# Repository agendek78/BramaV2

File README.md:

# BramaV2

**English** | [Polski](README.pl.md)

Gate control over Bluetooth LE: an Android app (with Android Auto support) and ESP32 controller firmware.
The phone is the BLE central; the ESP32 is the peripheral that drives two separate outputs (OPEN and CLOSE)
of the gate operator.

> **Status: prototype.** The project is tested on a single prototype board and three phones. It controls a
> physical device (a moving gate), so verify it yourself before using it in a real installation. Firmware images
> are signed with a development key; production Secure Boot, flash encryption and production keys are not part
> of this repository.

## What it does

- Two commands: `OPEN` (with optional automatic close after the connection is lost) and `CLOSE`.
- The gate position is always unknown: an acknowledgement only means that a pulse was driven on the output.
- Pairing with a QR code or the controller's 6-digit PIN (EC-JPAKE); the session is encrypted and authenticated
  with AES-256-GCM.
- Up to 8 authorized phones at the same time; the app can list phones, remove them and rename the current one.
- Automatic close is performed by the controller, without any involvement of the phone.
- Firmware update over BLE (OTA): signed ECDSA P-256 image, protection against an older `secure_version`,
  rollback to the previous version after a failed boot.
- Android Auto displays the interface of the app running on the phone.

## Repository layout

| Directory | Contents |
|---|---|
| `app/` | Android app (Kotlin, Jetpack Compose): screens and services |
| `protocol/` | Wire protocol: frames, cryptography, EC-JPAKE, test vectors |
| `domain/` | App logic, gate state and repository (no Android dependencies) |
| `ble/` | BLE layer (Android) and a simulated controller for tests |
| `car/` | Android Auto (Car App Library) |
| `firmware/` | ESP32 firmware (ESP-IDF v6.0.1, NimBLE) and host-side tests |
| `hw/` | PCB project in KiCad 10 (schematic, board, interactive BOM) |
| `doc/` | Specification, module designs, plans and implementation status |

The documentation is written in Polish. Good places to start:

- [`doc/PLAN_I_SPECYFIKACJA_BRAMY.md`](doc/PLAN_I_SPECYFIKACJA_BRAMY.md): specification and protocol,
- [`doc/implementation_status.md`](doc/implementation_status.md): what is done and verified (including on hardware),
- [`firmware/README.md`](firmware/README.md): firmware build, tests and configuration.

## Android app

Requirements: Android Studio with a JDK, Android SDK 37 (`compileSdk`), and a device running Android 13 (API 33)
or newer with Bluetooth LE. The QR scanner relies on Google Play services.

```sh
./gradlew :app:assembleDebug        # debug build
./gradlew :app:assembleRelease      # release build (R8, unsigned: the APK has to be signed)
./gradlew test                      # unit tests of all modules
```

The release build has R8 and resource shrinking enabled (about 4 MB). Keep rules for ML Kit are in
`app/proguard-rules.pro`. The repository contains no release signing configuration.

## Firmware

Requirements: ESP-IDF v6.0.1 (`~/.espressif/v6.0.1/esp-idf`) and a development key for signing the image.

```sh
cd firmware
tools/gen_dev_signing_key.sh        # once: key in ~/.config/brama/ (outside the repository)
tools/idf.sh set-target esp32       # once
tools/idf.sh build                  # produces the signed build/brama.bin
```

Host-side logic tests (target `linux`, need the `libbsd-dev` package):

```sh
cd firmware/test/host
../../tools/idf.sh --preview set-target linux
../../tools/idf.sh build && ./build/brama_host_test.elf
```

Details (prototype pins, service mode, UART console, OTA) are in [`firmware/README.md`](firmware/README.md).

**A note on eFuse.** On the board in `hw/`, GPIO12 has a pull-up that selects 1.8 V flash voltage at reset, while
the ESP32-WROOM-32D module has 3.3 V flash. The 3.3 V flash-voltage eFuse is therefore burned on every such board
(an irreversible step, done manually before the first boot; see `firmware/README.md`).

## Hardware

The board design is in `hw/` (KiCad 10, open `hw/esp32_brama.kicad_pro`): ESP32-WROOM-32D, power from an LMR54410
buck converter, two OPEN/CLOSE outputs through CNY17 optocouplers, an interlock input and a UART for diagnostics.
The project libraries are in `hw/lib/`. Notes from the board review are in `doc/implementation_status.md`.

## License

[MIT](LICENSE). The project is developed and tested by a single person; contributions and feedback are welcome.

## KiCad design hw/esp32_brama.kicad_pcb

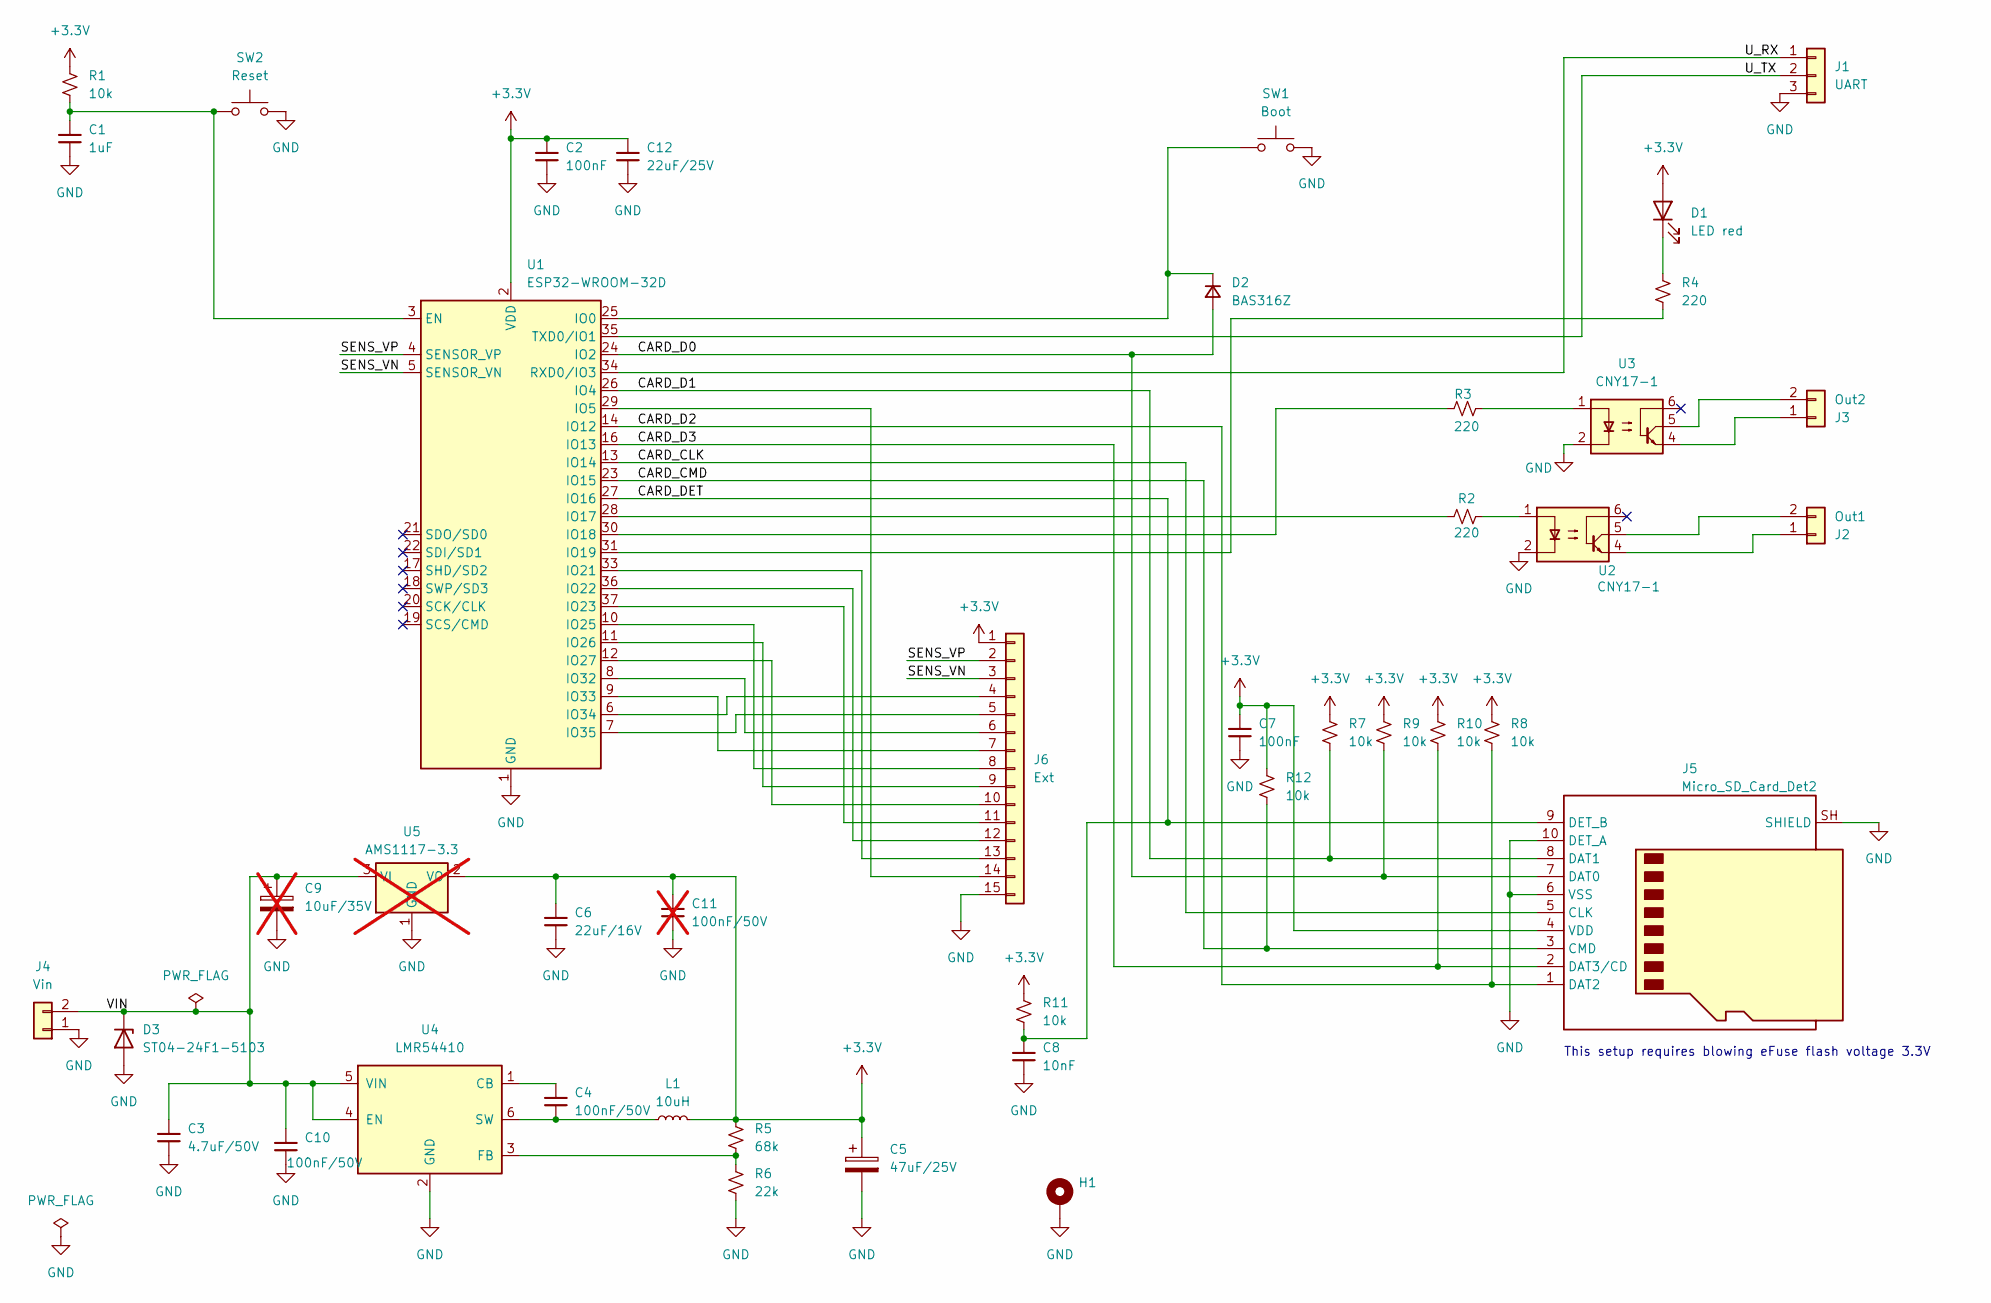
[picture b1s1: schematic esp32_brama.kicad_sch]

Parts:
C1: 1uF; C_0402_1005Metric
C2, C7: 100nF; C_0402_1005Metric
C3: 4.7uF/50V; C_0603_1608Metric
C4, C10: 100nF/50V; C_0402_1005Metric
C5: 47uF/25V; CP_Radial_D6.3mm_P2.50mm
C6: 22uF/16V; C_0805_2012Metric
C8: 10nF; C_0402_1005Metric
C9: 10uF/35V; CP_Radial_D6.3mm_P2.50mm; not fitted
C11: 100nF/50V; C_0402_1005Metric; not fitted
C12: 22uF/25V; C_0805_2012Metric
D1: LED red; D_0603_1608Metric
D2: BAS316Z; D_SOD-323_HandSoldering
D3: ST04-24F1-5103; D_SMA
H1: MountingHole_Pad; MountingHole_3.2mm_M3_ISO14580_Pad
J1: UART; PinHeader_1x03_P2.54mm_Vertical
J2: Out1; TerminalBlock_4Ucon_1x02_P3.50mm_Horizontal
J3: Out2; TerminalBlock_4Ucon_1x02_P3.50mm_Horizontal
J4: Vin; TerminalBlock_4Ucon_1x02_P3.50mm_Horizontal
J5: Micro_SD_Card_Det2; SD_MICRO
J6: Ext; PinHeader_1x15_P2.54mm_Vertical
L1: 10uH; L_Bourns-SRN4018
R1, R7, R8, R9, R10, R11, R12: 10k; R_0402_1005Metric
R2, R3, R4: 220; R_0402_1005Metric
R5: 68k; R_0402_1005Metric
R6: 22k; R_0402_1005Metric
SW1: Boot; SW_Tactile_SPST_NO_Straight_CK_PTS636Sx25SMTRLFS
SW2: Reset; SW_Tactile_SPST_NO_Straight_CK_PTS636Sx25SMTRLFS
U1: ESP32-WROOM-32D; ESP32-WROOM-32U
U2, U3: CNY17-1; DIP-6_W7.62mm
U4: LMR54410; SOT-23-6
U5: AMS1117-3.3; SOT-223-3_TabPin2; not fitted

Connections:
+3.3V: C2.1, C5.1, C6.1, C7.1, C11.1, C12.1, D1.2 (A), J5.4 (VDD), J6.1, L1.2, R1.1, R5.1, R7.1, R8.1, R9.1, R10.1, R11.1, R12.1, U1.2 (VDD), U5.2 (VO)
/CARD_CLK: J5.5 (CLK), U1.13 (IO14)
/CARD_CMD: J5.3 (CMD), R12.2, U1.23 (IO15)
/CARD_D0: D2.2 (A), J5.7 (DAT0), R9.2, U1.24 (IO2)
/CARD_D1: J5.8 (DAT1), R7.2, U1.26 (IO4)
/CARD_D2: J5.1 (DAT2), R8.2, U1.14 (IO12)
/CARD_D3: J5.2 (DAT3/CD), R10.2, U1.16 (IO13)
/CARD_DET: C8.1, J5.9 (DET_B), R11.2, U1.27 (IO16)
/SENS_VN: J6.3, U1.5 (SENSOR_VN)
/SENS_VP: J6.2, U1.4 (SENSOR_VP)
/U_RX: J1.1, U1.34 (RXD0/IO3)
/U_TX: J1.2, U1.35 (TXD0/IO1)
/VIN: C3.1, C9.1, C10.1, D3.1 (K), J4.2, U4.4 (EN), U4.5 (VIN), U5.3 (VI)
GND: C1.2, C2.2, C3.2, C5.2, C6.2, C7.2, C8.2, C9.2, C10.2, C11.2, C12.2, D3.2 (A), H1.1 (1_1), J1.3, J4.1, J5.6 (VSS), J5.10 (DET_A), J5.SH (SHIELD), J6.15, R6.2, SW1.2, SW2.2, U1.1 (GND), U1.15 (GND), U1.38 (GND), U1.39 (GND), U2.2, U3.2, U4.2 (GND), U5.1 (GND)
unnamed: D1.1 (K), R4.2
unnamed: D2.1 (K), SW1.1, U1.25 (IO0)
unnamed: J2.1, U2.4
unnamed: J2.2, U2.5
unnamed: J3.1, U3.4
unnamed: J3.2, U3.5
unnamed: J6.4, U1.6 (IO34)
unnamed: J6.5, U1.7 (IO35)
unnamed: J6.6, U1.8 (IO32)
unnamed: J6.7, U1.9 (IO33)
unnamed: J6.8, U1.10 (IO25)
unnamed: J6.9, U1.11 (IO26)
unnamed: J6.10, U1.12 (IO27)
unnamed: J6.11, U1.37 (IO23)
unnamed: J6.12, U1.36 (IO22)
unnamed: J6.13, U1.33 (IO21)
unnamed: J6.14, U1.29 (IO5)
unnamed: R2.2, U2.1
unnamed: R3.2, U3.1
unnamed: C1.1, R1.2, SW2.1, U1.3 (EN)
unnamed: R2.1, U1.28 (IO17)
unnamed: R3.1, U1.30 (IO18)
unnamed: R4.1, U1.31 (IO19)
unnamed: C4.1, U4.1 (CB)
unnamed: R5.2, R6.1, U4.3 (FB)
unnamed: C4.2, L1.1, U4.6 (SW)

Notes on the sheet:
This setup requires blowing eFuse flash voltage 3.3V

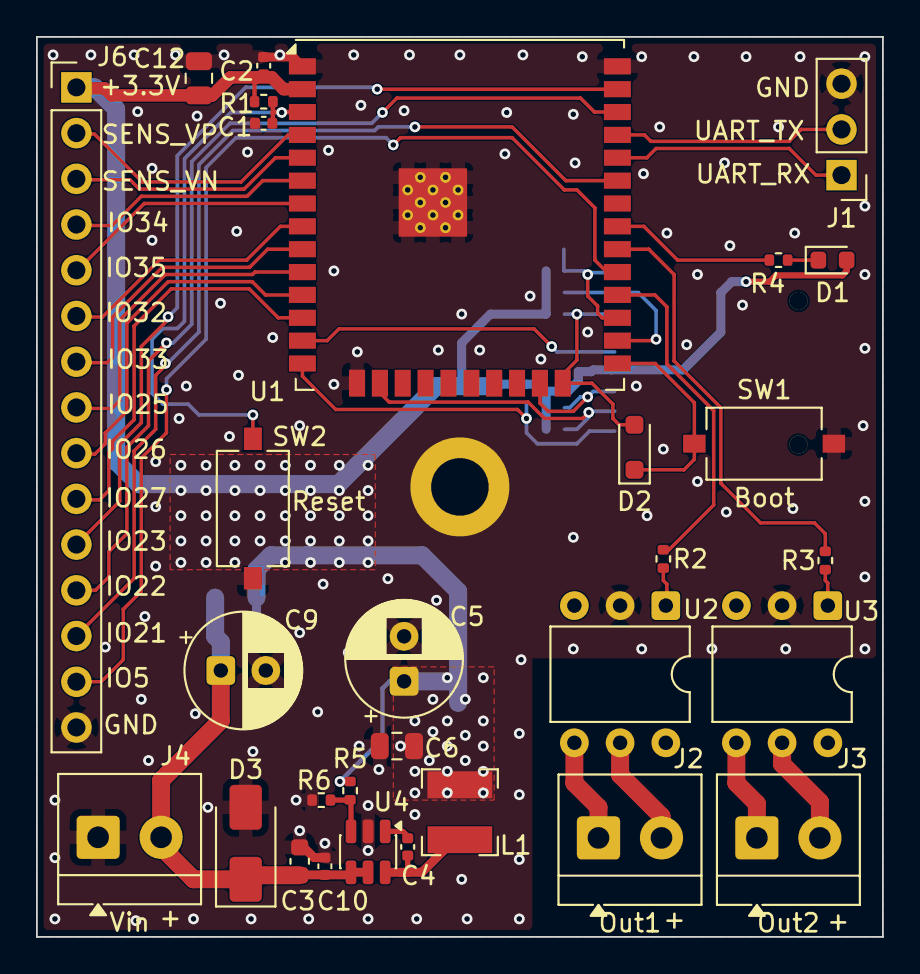
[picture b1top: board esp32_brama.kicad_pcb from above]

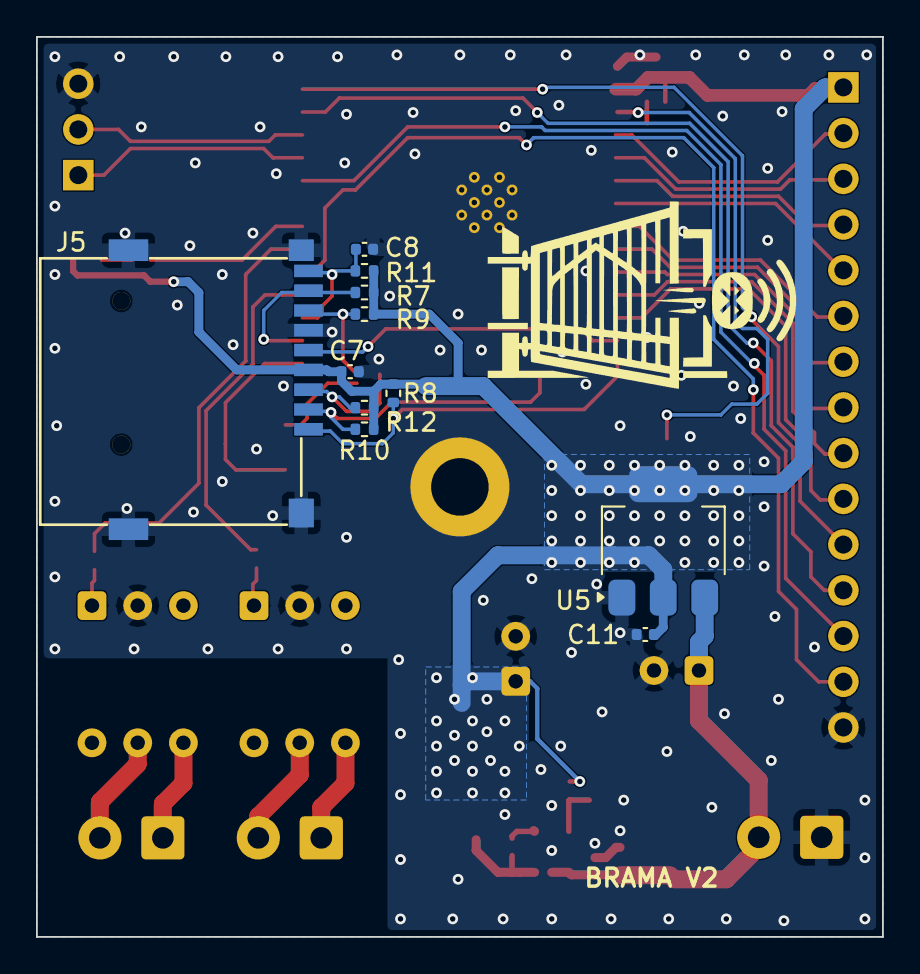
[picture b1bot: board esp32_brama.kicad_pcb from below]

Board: 2 copper layers, 47.0 x 50.0 mm, 42 parts (11 on the bottom side), 40 nets.
